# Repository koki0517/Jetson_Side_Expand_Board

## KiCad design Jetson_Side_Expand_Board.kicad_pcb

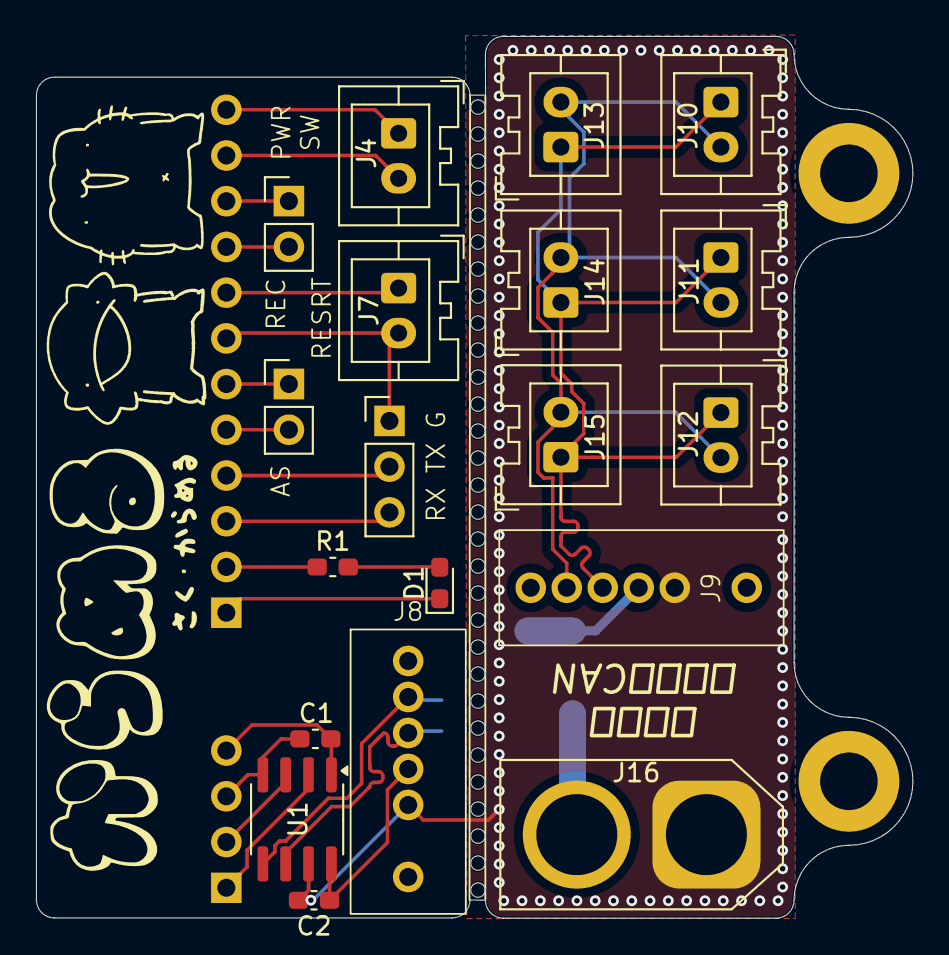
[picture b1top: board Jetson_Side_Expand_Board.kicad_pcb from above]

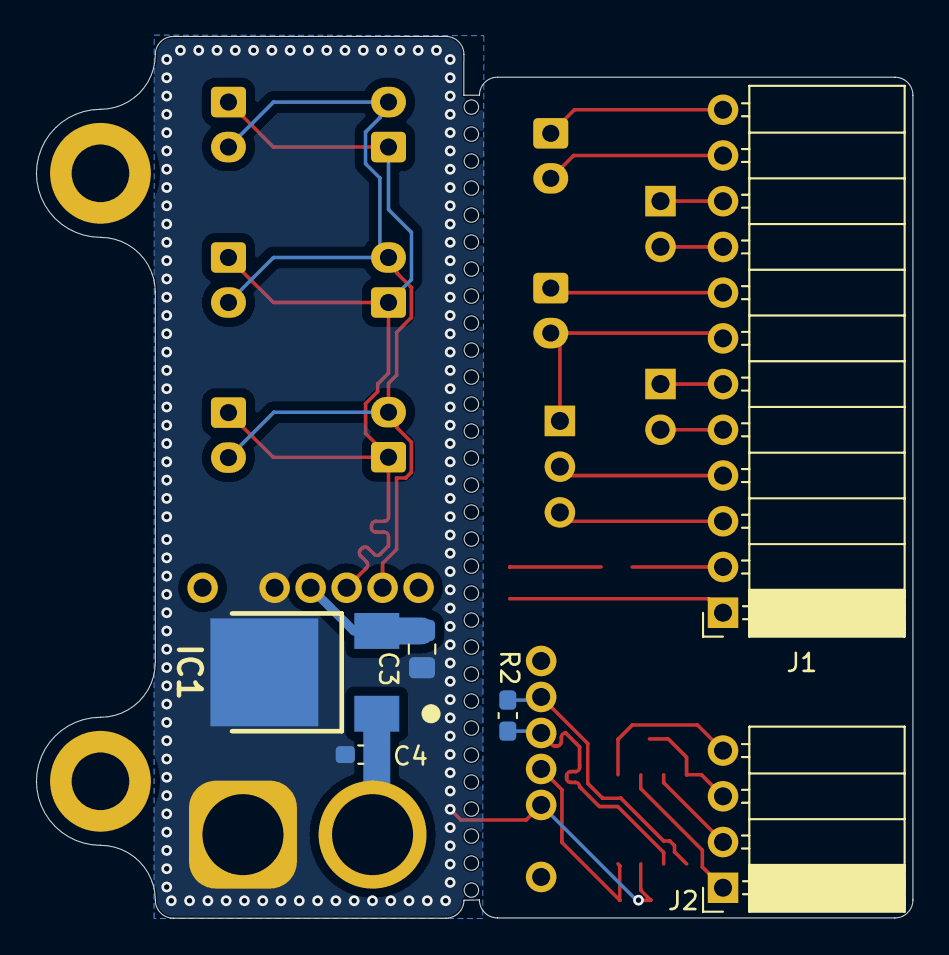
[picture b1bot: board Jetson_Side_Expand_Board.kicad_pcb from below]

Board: 6 copper layers, 48.7 x 49.0 mm, 25 parts (6 on the bottom side), 21 nets.

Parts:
C1, C2, C4: 100n; C_0603_1608Metric_Pad1.08x0.95mm_HandSolder
C3: 10u; C_0805_2012Metric_Pad1.18x1.45mm_HandSolder
D1: RED; LED_0603_1608Metric_Pad1.05x0.95mm_HandSolder
IC1: NJM2391DL1-05-TE1; TO-252-3-L1_1
J1: Conn_01x12_Socket; PinSocket_1x12_P2.54mm_Horizontal
J2: Conn_01x04_Socket; PinSocket_1x04_P2.54mm_Horizontal
J3, J5: Conn_01x02_Pin; PinHeader_1x02_P2.54mm_Vertical
J4, J7, J10, J11, J12, J13, J14, J15: Conn_01x02; JST_XA_B02B-XASK-1_1x02_P2.50mm_Vertical
J6: Conn_01x03_Pin; PinHeader_1x03_P2.54mm_Vertical
J8: Conn_01x04; e-CON_1×04
J9: e-CON; e-CON_1×04
J16: 24V; AMASS_XT60-M_1x02_P7.20mm_Vertical
R1: 1k; C_0603_1608Metric_Pad1.08x0.95mm_HandSolder
R2: 120; C_0603_1608Metric_Pad1.08x0.95mm_HandSolder
U1: SOIC-8_3.9x4.9mm_P1.27mm

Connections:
+3.3V: C1.1, J2.4, U1.1 (VCC1)
+5V: C2.1, C3.1, IC1.2 (VOUT), J8.2, J9.2, U1.8 (VCC2)
/Auto_Start1: J1.5, J5.2
/Auto_Start2: J1.6, J5.1
/CAN+: J8.3, R2.1, U1.6 (CANH)
/CAN-: J8.4, R2.2, U1.5 (CANL)
/CAN_RX: J2.2, U1.3 (RXD)
/CAN_TX: J2.1, U1.2 (TXD)
/DCDC5V/CAN+: J9.3, J10.1, J11.1, J12.1, J13.1, J14.1, J15.1
/DCDC5V/CAN-: J9.4, J10.2, J11.2, J12.2, J13.2, J14.2, J15.2
/FORCE_RECOVERY: J1.10, J3.1
/PC_LED+: J1.2, R1.1
/PC_LED-: D1.1 (K), J1.1
/SLEEP/WAKE: J1.12, J4.1
/SYS_RESET: J1.8, J7.1
/UART2_RXD (DEBUG): J1.3, J6.3
/UART2_TXD (DEBUG): J1.4, J6.2
GND: C1.2, J1.7, J1.9, J1.11, J2.3, J3.2, J4.2, J6.1, J7.2, U1.4 (GND1)
GND1: C2.2, C3.2, C4.2, IC1.3 (GND), J8.1, J9.1, J16.1, U1.7 (GND2)
unnamed: D1.2 (A), R1.2
VDD: C4.1, IC1.1 (VIN), J16.2

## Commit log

2025-12-14 init kicad file
2025-12-21 セラコンのGND
2025-12-21 5Vを24Vからレギュレータで作る
